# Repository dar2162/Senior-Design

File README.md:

# Senior-Design
Narwhal Power Supply

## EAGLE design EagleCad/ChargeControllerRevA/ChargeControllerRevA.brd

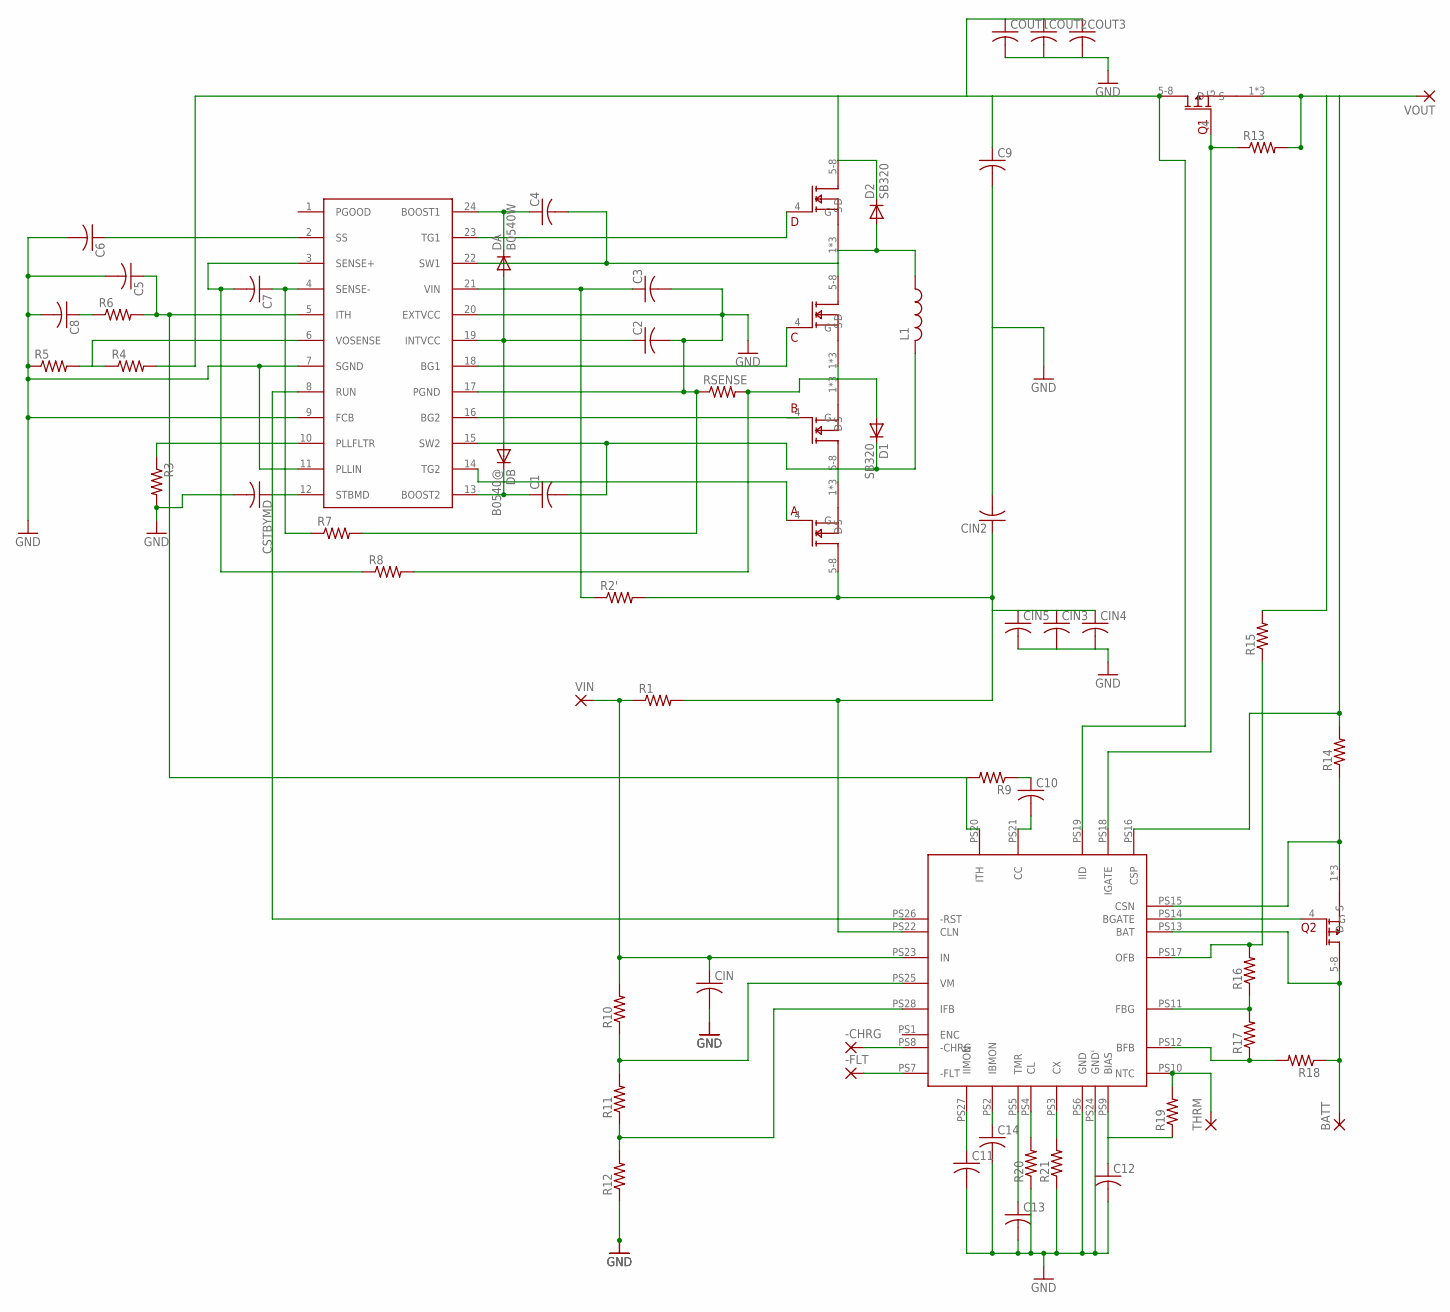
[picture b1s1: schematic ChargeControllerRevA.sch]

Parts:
-CHRG: 3,81/1,4
-FLT: 3,81/1,4
A: SI7884DP; POWERPAK-SO-08
B: SI7884DP; POWERPAK-SO-08
BATT: 3,81/1,4
C: SI7884DP; POWERPAK-SO-08
C1, C2, C3, C4, C5, C6, C7, C8, C9, C10, C11, C12, C13, C14: C-US025-050X050; C025-050X050
CIN, CIN2, CIN3, CIN4, CIN5: C-US025-050X050; C025-050X050
COUT1, COUT2, COUT3: C-US025-050X050; C025-050X050
CSTBYMD: C-US025-050X050; C025-050X050
D: SI7884DP; POWERPAK-SO-08
D1, D2: SB320; DO201-15
DA: B0540W; SOD123
DB: B0540@; SOD123
L1: L-US6000-XXX-RC; 6000-XXXX-RC
Q1, Q2: SI7135DP; POWERPAK-SO-08
R1, R2', R3, R4, R5, R6, R7, R8, R9, R10, R11, R12, R13, R14, R15, R16, R17, R18, R19, R20, R21: R-US_0309/12; 0309/12
RSENSE: R-US_0309/12; 0309/12
THRM: 3,81/1,4
U$1: LT3780; SSOP24
U$2: LTC4000-1; SSOP-28_GN
VIN: 3,81/1,4
VOUT: 3,81/1,4

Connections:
BATT: BATT.1, Q2.5-8 (D), R18.1, U$2.PS13 (BAT)
GND: C2.2, C3.2, C5.2, C6.2, C8.2, C9.2, C11.2, C12.2, C13.2, C14.2, CIN.2, CIN2.2, CIN3.2, CIN4.2, CIN5.2, COUT1.2, COUT2.2, COUT3.2, CSTBYMD.2, R3.2, R5.1, R7.2, R12.1, R20.1, R21.1, RSENSE.1, U$1.7 (SGND), U$1.9 (FCB), U$1.11 (PLLIN), U$1.17 (PGND), U$1.20 (EXTVCC), U$2.PS6 (GND), U$2.PS24 (GND')
unnamed: C6.1, U$1.2 (SS)
unnamed: C7.1, R7.1, U$1.4 (SENSE-)
unnamed: C7.2, R8.1, U$1.3 (SENSE+)
unnamed: C5.1, R6.2, R9.2, U$1.5 (ITH), U$2.PS20 (ITH)
unnamed: C8.1, R6.1
unnamed: R4.1, R5.2, U$1.6 (VOSENSE)
unnamed: B.4 (G), U$1.16 (BG2)
unnamed: R3.1, U$1.10 (PLLFLTR)
unnamed: C4.1, DA.C, U$1.24 (BOOST1)
unnamed: C3.1, R2'.1, U$1.21 (VIN)
unnamed: C2.1, DA.A, DB.A, U$1.19 (INTVCC)
unnamed: CSTBYMD.1, U$1.12 (STBMD)
unnamed: B.1 (S), B.2 (S), B.3 (S), C.1 (S), C.2 (S), C.3 (S), D1.A, R8.2, RSENSE.2
unnamed: U$1.8 (RUN), U$2.PS26 (-RST)
unnamed: C10.1, R9.1
unnamed: C1.1, DB.C, U$1.13 (BOOST2)
unnamed: Q1.1 (S), Q1.2 (S), Q1.3 (S), R13.2, R14.2, R15.2, U$2.PS16 (CSP), VOUT.1
unnamed: D.4 (G), U$1.23 (TG1)
unnamed: C.4 (G), U$1.18 (BG1)
unnamed: A.4 (G), U$1.14 (TG2)
unnamed: Q1.4 (G), R13.1, U$2.PS18 (IGATE)
unnamed: C10.2, U$2.PS21 (CC)
unnamed: R10.1, R11.2, U$2.PS25 (VM)
unnamed: R11.1, R12.2, U$2.PS28 (IFB)
unnamed: -FLT.1, U$2.PS7 (-FLT)
unnamed: C11.1, U$2.PS27 (IIMON)
unnamed: C14.1, U$2.PS2 (IBMON)
unnamed: C13.1, U$2.PS5 (TMR)
unnamed: R20.2, U$2.PS4 (CL)
unnamed: R21.2, U$2.PS3 (CX)
unnamed: C12.1, R19.1, U$2.PS9 (BIAS)
unnamed: -CHRG.1, U$2.PS8 (-CHRG)
unnamed: R19.2, THRM.1, U$2.PS10 (NTC)
unnamed: R16.1, R17.2, U$2.PS11 (FBG)
unnamed: R17.1, R18.2, U$2.PS12 (BFB)
unnamed: R15.1, R16.2, U$2.PS17 (OFB)
unnamed: Q2.4 (G), U$2.PS14 (BGATE)
unnamed: Q2.1 (S), Q2.2 (S), Q2.3 (S), R14.1, U$2.PS15 (CSN)
SW1: C.5-8 (D), C4.2, D.1 (S), D.2 (S), D.3 (S), D2.A, L1.1, U$1.22 (SW1)
SW2: A.1 (S), A.2 (S), A.3 (S), B.5-8 (D), C1.2, D1.C, L1.2, U$1.15 (SW2)
VIN: A.5-8 (D), CIN2.1, CIN3.1, CIN4.1, CIN5.1, R1.2, R2'.2, U$2.PS22 (CLN)
VIN+: CIN.1, R1.1, R10.2, U$2.PS23 (IN), VIN.1
VOUT(1): C9.1, COUT1.1, COUT2.1, COUT3.1, D.5-8 (D), D2.C, Q1.5-8 (D), R4.2, U$2.PS19 (IID)

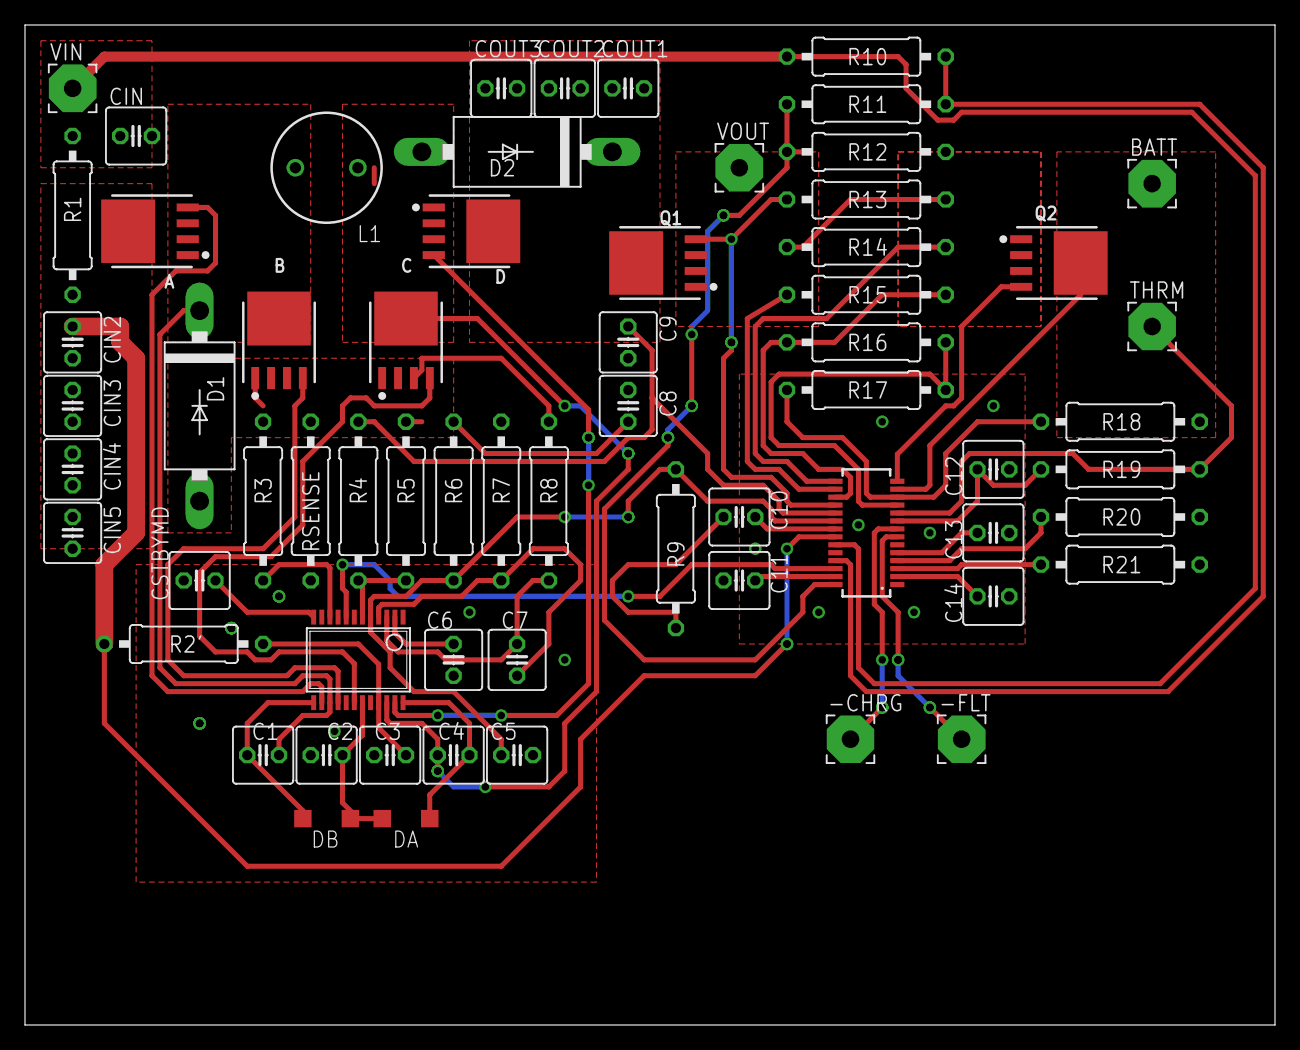
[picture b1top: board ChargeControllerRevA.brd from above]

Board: 2 copper layers, 100.0 x 80.0 mm, 64 parts (0 on the bottom side), 45 nets.

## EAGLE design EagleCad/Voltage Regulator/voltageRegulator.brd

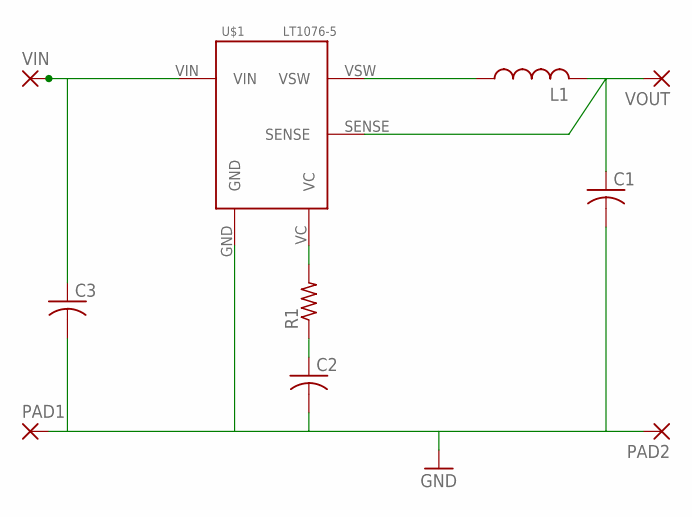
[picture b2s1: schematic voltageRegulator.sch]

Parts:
C1, C3: C-US025-060X050; C025-060X050
C2: C-US025-030X050; C025-030X050
L1: L-US6000-XXX-RC; 6000-XXXX-RC
PAD1, PAD2: 3,81/1,4
R1: R-US_0204/7; 0204/7
U$1: LT1076-5; TO220-5
VIN: 3,81/1,4
VOUT: 3,81/1,4

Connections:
GND: C1.2, C2.2, C3.2, PAD1.1, PAD2.1, U$1.GND
unnamed: R1.2, U$1.VC
unnamed: C2.1, R1.1
unnamed: C3.1, U$1.VIN, VIN.1
unnamed: L1.1, U$1.VSW
unnamed: C1.1, L1.2, U$1.SENSE, VOUT.1

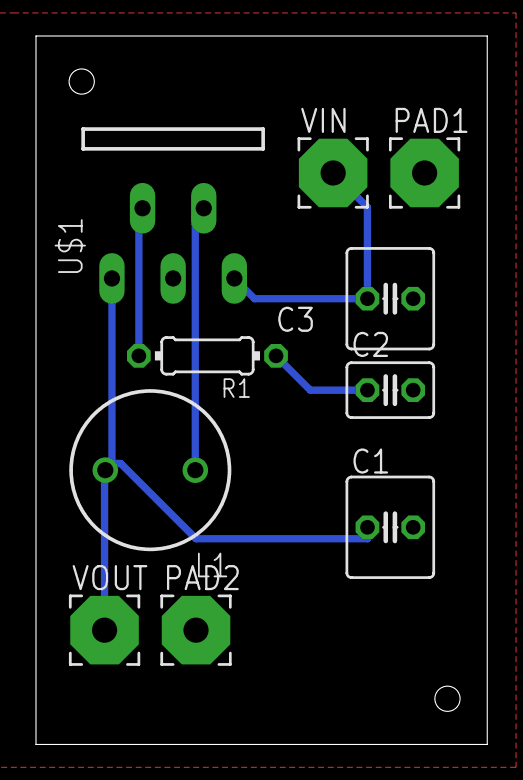
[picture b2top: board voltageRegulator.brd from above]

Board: 2 copper layers, 25.1 x 39.4 mm, 10 parts (0 on the bottom side), 6 nets.

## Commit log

2015-03-31 :circus_tent: Added .gitattributes & .gitignore files
2015-03-31 init
2015-03-31 renamed RC
2015-04-01 Libr added
2015-04-01 in/out caps added
